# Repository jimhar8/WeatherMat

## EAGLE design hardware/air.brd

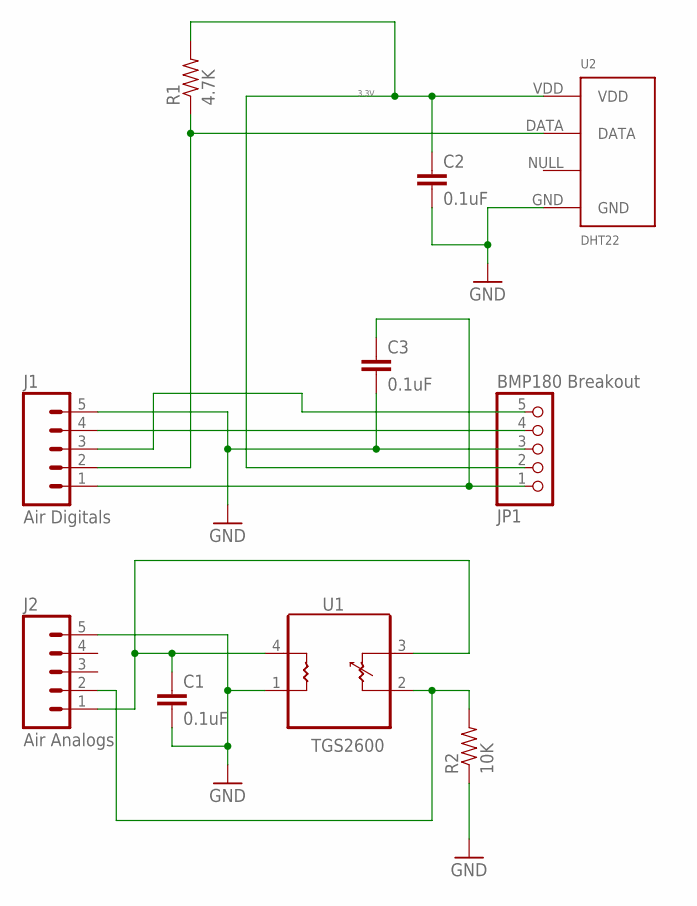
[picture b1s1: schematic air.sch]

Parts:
C1, C2, C3: 0.1uF; CAP-PTH-SMALL
J1: Air Digitals; SCREWTERMINAL-3.5MM-5
J2: Air Analogs; SCREWTERMINAL-3.5MM-5
JP1: BMP180 Breakout; 1X05_ROUND_70
R1: 4.7K; AXIAL-0.4
R2: 10K; AXIAL-0.4
U1: TGS2600; TO5_AIRQ
U2: DHT22; AM2302

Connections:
3.3V: C2.1, JP1.2, R1.P$2 (2), U2.VDD
GND: C1.2, C2.2, C3.2, J1.5, J2.5, JP1.3, R2.P$1 (1), U1.1, U2.GND
unnamed: C3.1, J1.1, JP1.1
unnamed: J1.4, JP1.4
unnamed: J1.2, R1.P$1 (1), U2.DATA
unnamed: J2.2, R2.P$2 (2), U1.2
unnamed: C1.1, J2.1, U1.3, U1.4
SDA: J1.3, JP1.5

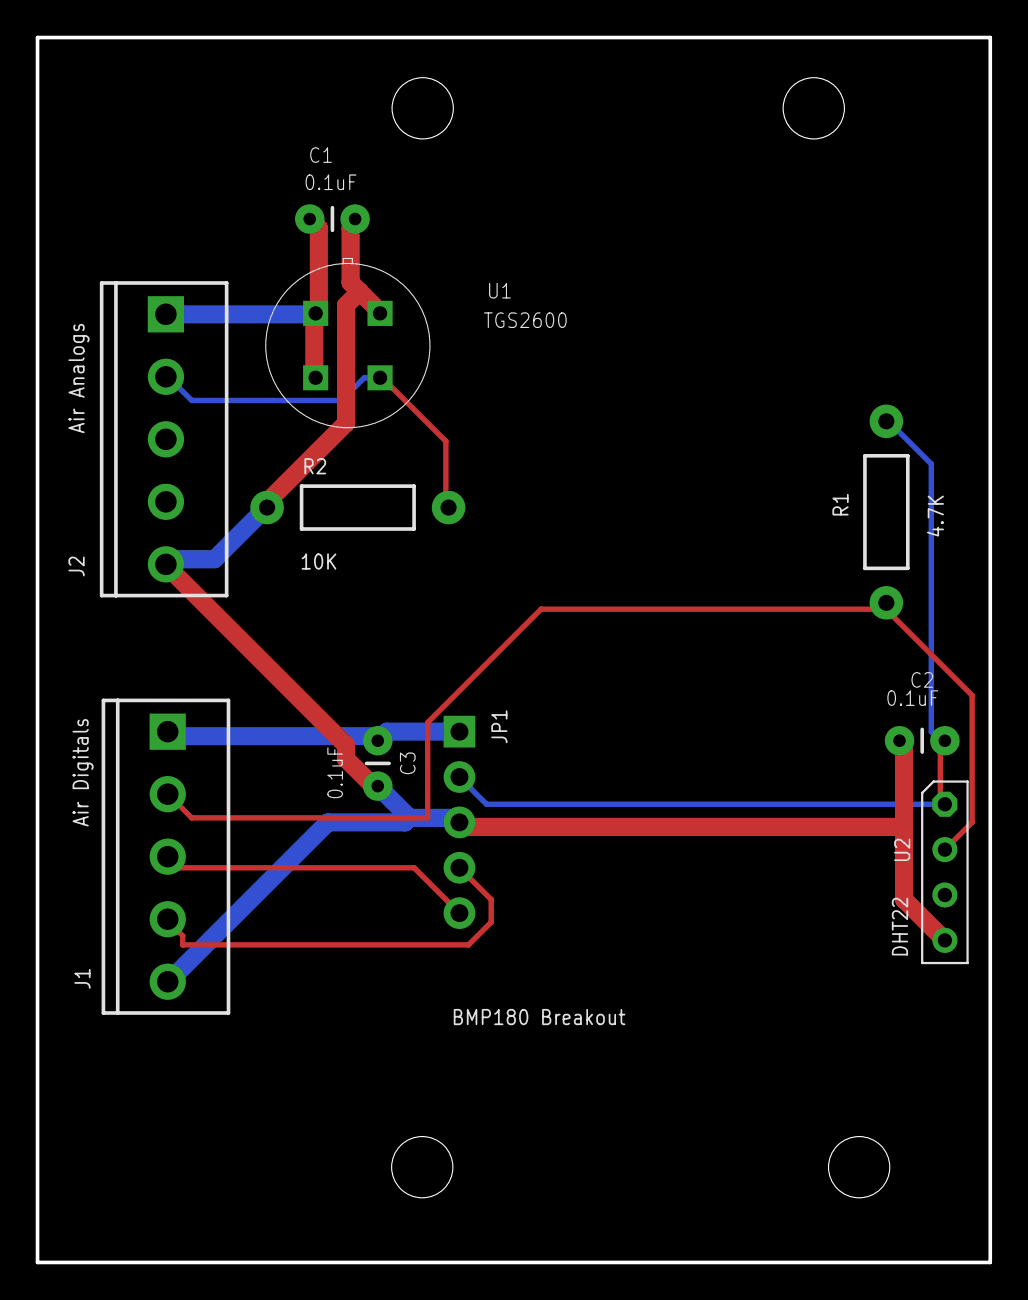
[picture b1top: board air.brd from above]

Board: 2 copper layers, 53.3 x 68.6 mm, 10 parts (0 on the bottom side), 8 nets.

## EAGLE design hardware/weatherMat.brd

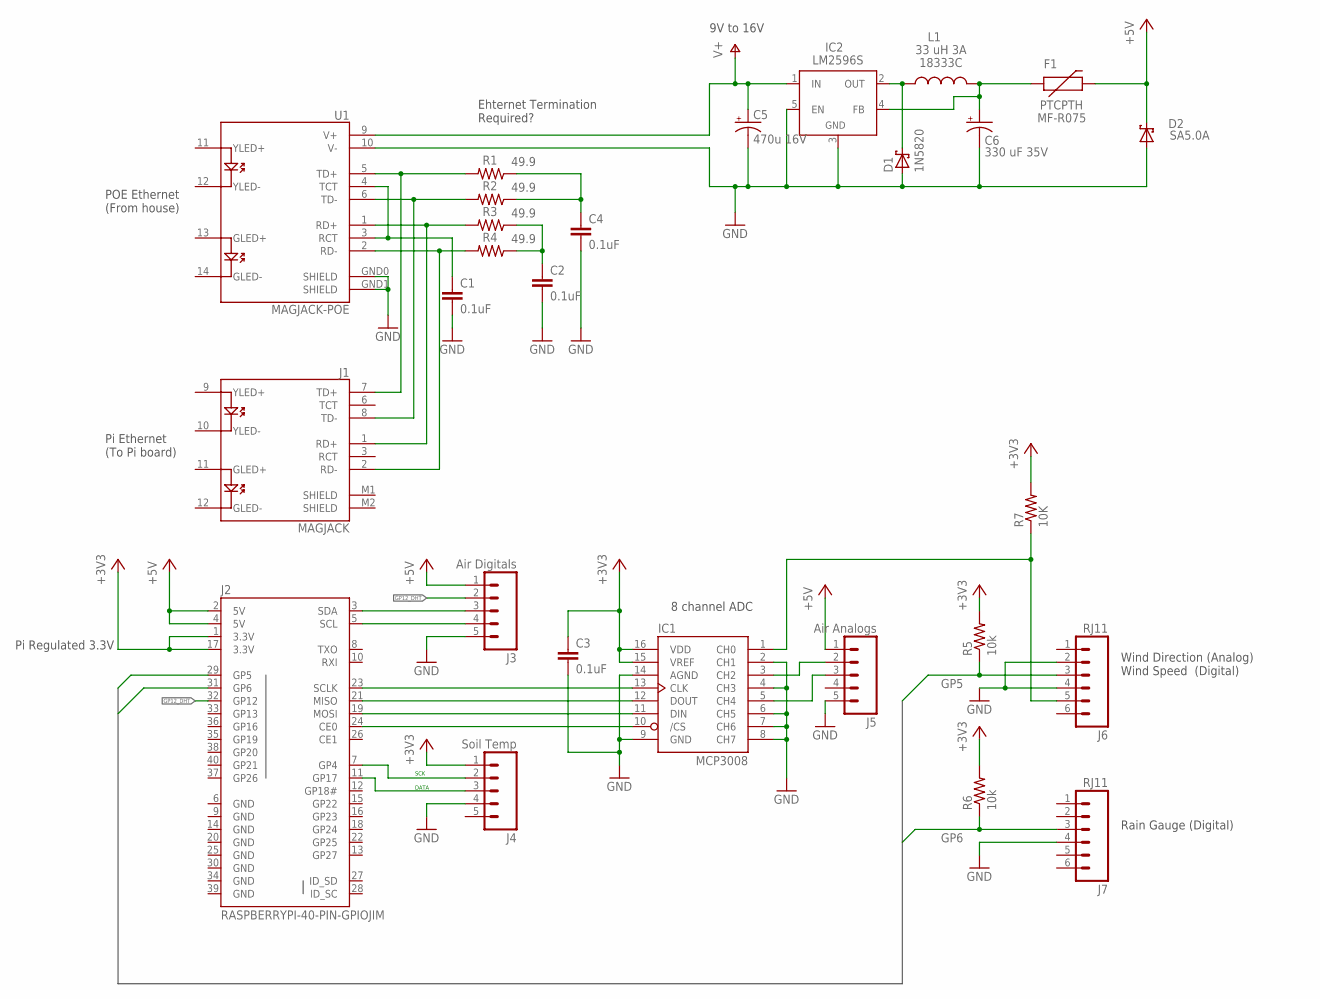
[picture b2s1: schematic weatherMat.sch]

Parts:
C1, C2, C3, C4: 0.1uF; CAP-PTH-SMALL
C5: 470u 16V; CPOL-RADIAL-470UF-16V
C6: 330 uF 35V; CPOL-RADIAL-100UF-25V
D1: 1N5820; DO201T15
D2: SA5.0A; DO15-12
F1: PTCPTH; PTC; PARTNUM MF-R075
IC1: MCP3008; DIL16
IC2: LM2596S; TO220-51
J1: MAGJACK
J2: RASPBERRYPI-40-PIN-GPIOJIM; 2X20-JIM
J3: Air Digitals; SCREWTERMINAL-3.5MM-5
J4: Soil Temp; SCREWTERMINAL-3.5MM-5
J5: Air Analogs; SCREWTERMINAL-3.5MM-5
J6, J7: RJ11; RJ11-6
L1: 33 uH 3A; MURATA; PARTNUM 18333C
R1, R2, R3, R4: 49.9; AXIAL-0.4
R5, R6: 10k; AXIAL-0.4
R7: 10K; AXIAL-0.4
U1: MAGJACK-POE

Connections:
+3V3: C3.1, IC1.15 (VREF), IC1.16 (VDD), J2.1 (3.3V), J2.17 (3.3V), J4.1, R5.P$2 (2), R6.P$2 (2), R7.P$2 (2)
+5V: D2.C, F1.P$2 (2), J2.2 (5V), J2.4 (5V), J3.1, J5.1
GND: C1.2, C2.2, C3.2, C4.2, C5.2 (-), C6.2 (-), D1.A, D2.A, IC1.2 (CH1), IC1.4 (CH3), IC1.6 (CH5), IC1.7 (CH6), IC1.8 (CH7), IC1.9 (GND), IC1.14 (AGND), IC2.3 (GND), IC2.5 (EN), J2.6 (GND), J2.9 (GND), J2.14 (GND), J2.20 (GND), J2.25 (GND), J2.30 (GND), J2.34 (GND), J2.39 (GND), J3.5, J4.4, J5.5, J6.2, J6.4, J7.4, U1.10 (V-), U1.GND0 (SHIELD), U1.GND1 (SHIELD)
GP5: J2.29 (GP5), J6.3, R5.P$1 (1)
GP6: J2.31 (GP6), J7.3, R6.P$1 (1)
GP12_DHT: J2.32 (GP12), J3.2
unnamed: D1.C, IC2.2 (OUT), L1.P$1 (1)
unnamed: C1.1, U1.3 (RCT), U1.4 (TCT)
unnamed: J1.7 (TD+), R1.P$2 (2), U1.5 (TD+)
unnamed: J1.8 (TD-), R2.P$2 (2), U1.6 (TD-)
unnamed: J1.1 (RD+), R3.P$2 (2), U1.1 (RD+)
unnamed: J1.2 (RD-), R4.P$2 (2), U1.2 (RD-)
unnamed: C4.1, R1.P$1 (1), R2.P$1 (1)
unnamed: C2.1, R3.P$1 (1), R4.P$1 (1)
unnamed: IC1.12 (DOUT), J2.21 (MISO)
unnamed: IC1.11 (DIN), J2.19 (MOSI)
unnamed: IC1.13 (CLK), J2.23 (SCLK)
unnamed: IC1.10 (/CS), J2.24 (CE0)
unnamed: IC1.1 (CH0), J6.5, R7.P$1 (1)
unnamed: C6.1 (+), F1.P$1 (1), IC2.4 (FB), L1.P$3 (2)
unnamed: J2.3 (SDA), J3.3
unnamed: J2.5 (SCL), J3.4
unnamed: IC1.3 (CH2), J5.2
unnamed: IC1.5 (CH4), J5.3
unnamed: J2.11 (GP17), J4.3
unnamed: J2.7 (GP4), J4.2
V+: C5.1 (+), IC2.1 (IN), U1.9 (V+)

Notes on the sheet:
Wind Direction (Analog) Wind Speed (Digital)
Rain Gauge (Digital)
POE Ethernet (From house)
Pi Ethernet (To Pi board)
Pi Regulated 3.3V
9V to 16V
DATA
SCK
Ehternet Termination Required?
8 channel ADC

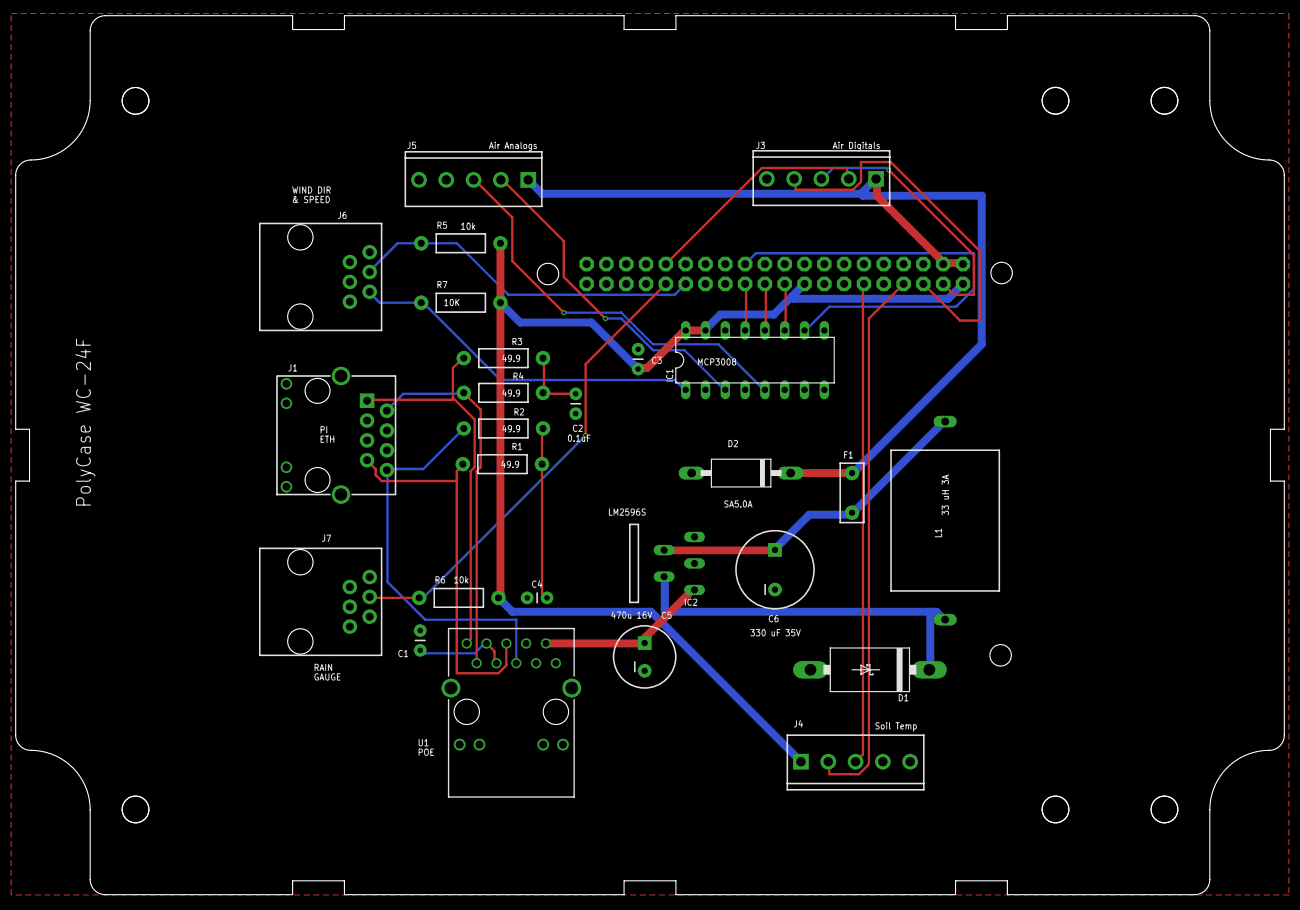
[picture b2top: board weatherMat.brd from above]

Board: 2 copper layers, 162.7 x 112.7 mm, 28 parts (1 on the bottom side), 27 nets.

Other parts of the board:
U$2: WC-24F

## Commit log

2016-03-01 remove stuff
2016-03-03 pdf file
2016-03-03 Push gerbers
2016-03-03 Added air board stuff
2016-03-04 update ignore list
2016-03-07 Test from linux
2016-03-07 Initial commit for DHT22 Lua stuff
2016-03-11 Board update
2016-03-11 Gerber updates
2016-03-14 Restructuring
2016-03-14 BMP changes
2016-03-17 Wind calculations and script
2016-03-20 board updates
2016-03-20 Some modules
2016-03-21 Add source
2016-03-25 Renaming DHT files
2016-03-25 More rearrangement
2016-03-25 More cleanup
2016-03-25 Rename dirs
2016-03-25 python gpio example
2016-04-02 eagle updates
2016-04-30 soil sensor updates
2016-05-06 remove light sensor from air board
2016-05-06 Revise for Ambient Weather SRS100
2016-05-14 decoupling caps
2016-05-23 remove light directory

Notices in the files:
parts and their libraries:
SparkFun-Connectors: Licensing: CC v3.0 Share-Alike You are welcome to use this library for commercial purposes.
SparkFun-Passives: Licensing: Creative Commons ShareAlike 4.0 International - https://creativecommons.org/licenses/by-sa/4.0
